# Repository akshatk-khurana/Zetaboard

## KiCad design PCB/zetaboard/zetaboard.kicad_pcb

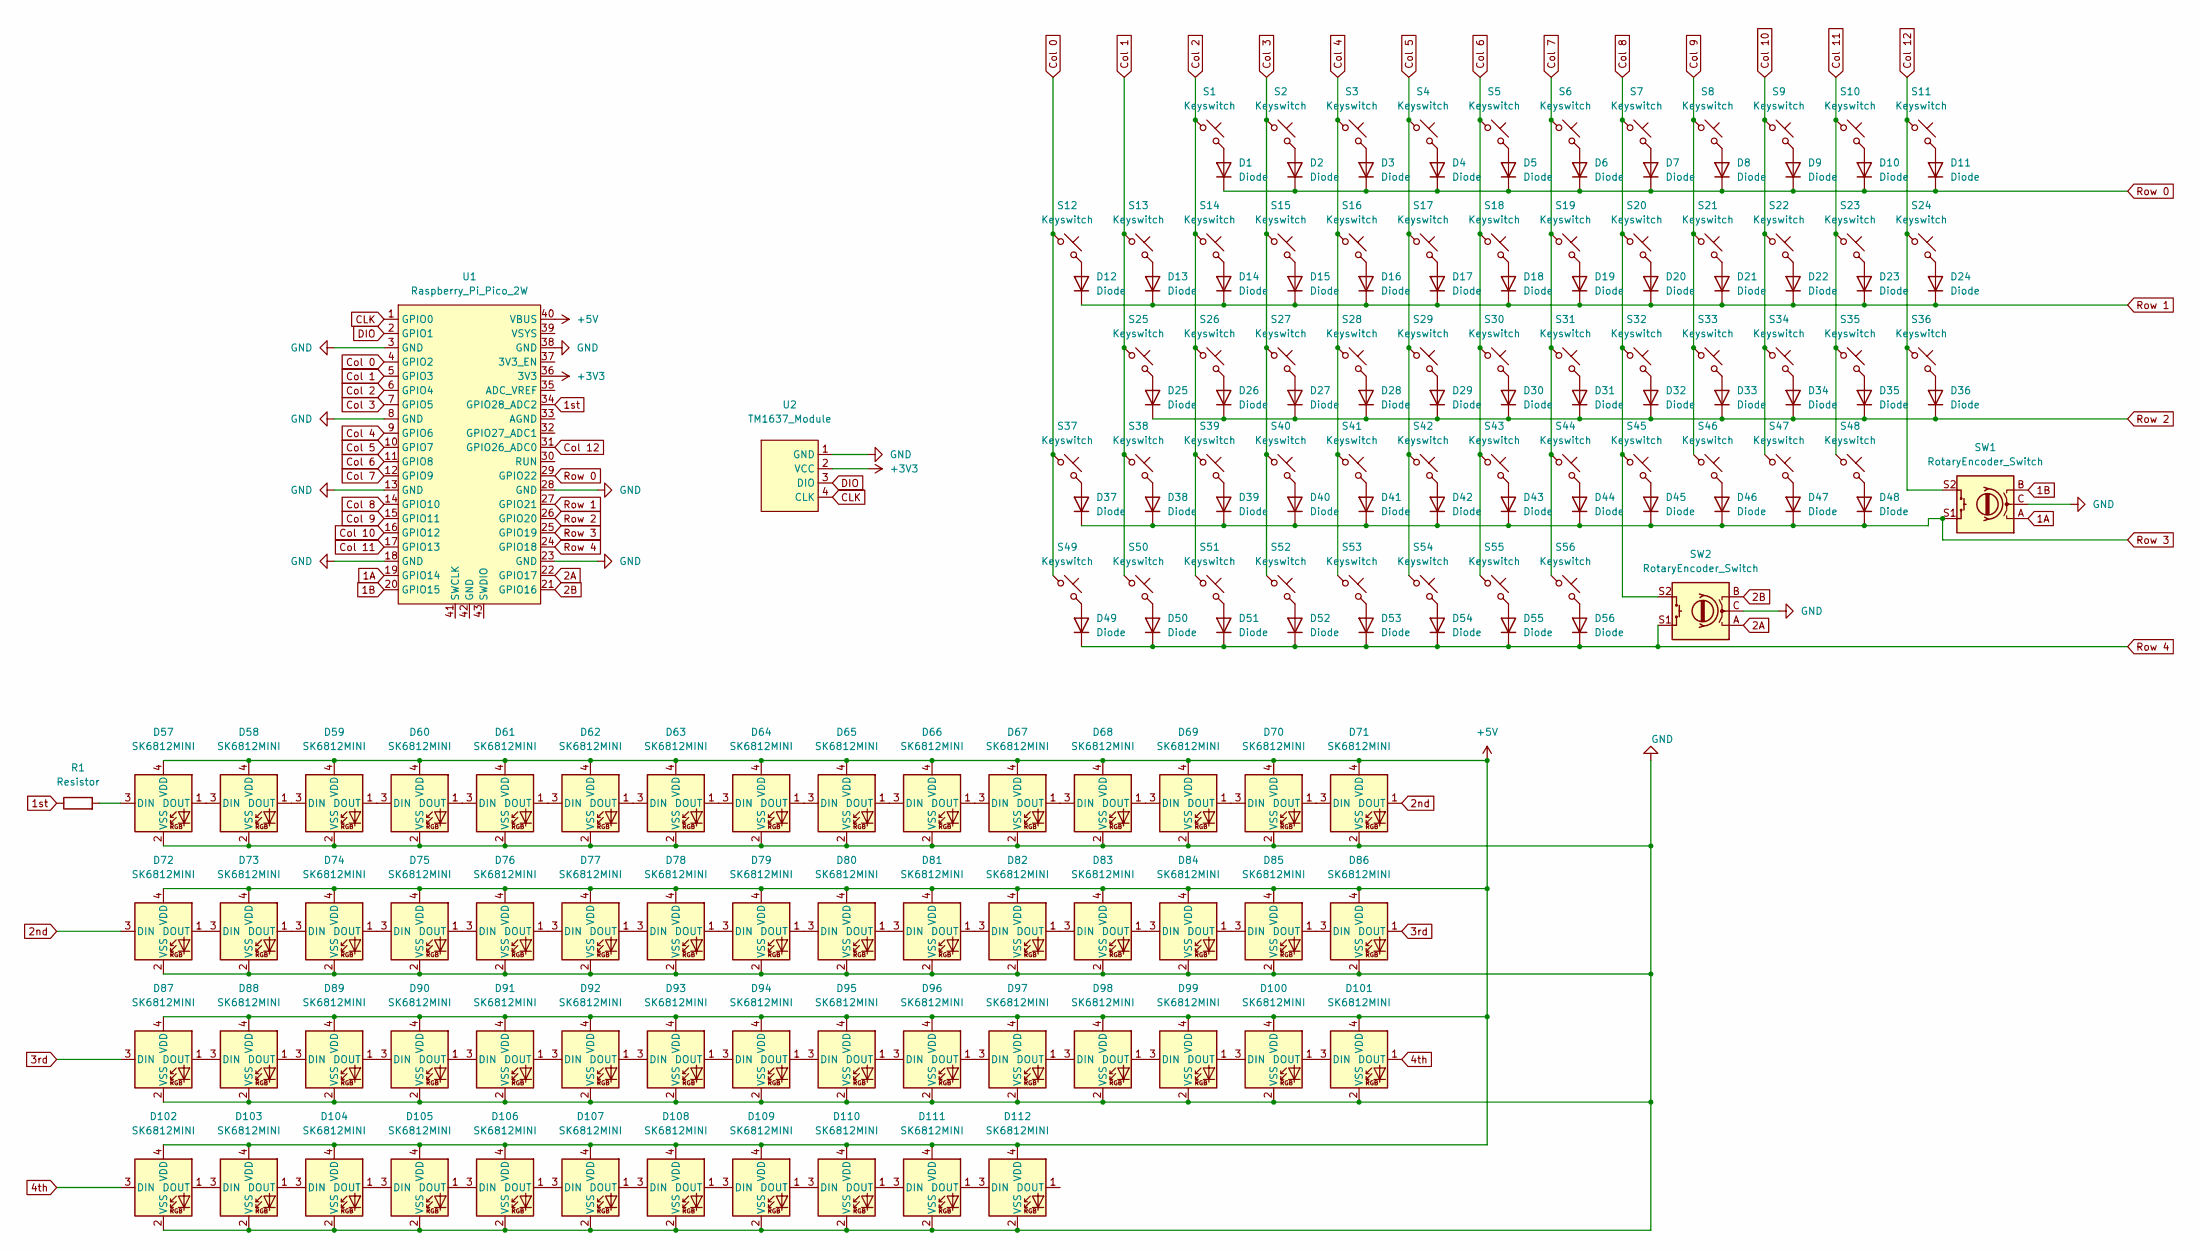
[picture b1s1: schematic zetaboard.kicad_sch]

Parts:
D1, D2, D3, D4, D5, D6, D7, D8, D9, D10, D11, D12, D13, D14, D15, D16, D17, D18, D19, D20, D21, D22, D23, D24, D25, D26, D27, D28, D29, D30, D31, D32, D33, D34, D35, D36, D37, D38, D39, D40, D41, D42, D43, D44, D45, D46, D47, D48, D49, D50, D51, D52, D53, D54, D55, D56: Diode; Diode_DO-35
D57, D58, D59, D60, D61, D62, D63, D64, D65, D66, D67, D68, D69, D70, D71, D72, D73, D74, D75, D76, D77, D78, D79, D80, D81, D82, D83, D84, D85, D86, D87, D88, D89, D90, D91, D92, D93, D94, D95, D96, D97, D98, D99, D100, D101, D102, D103, D104, D105, D106, D107, D108, D109, D110, D111, D112: SK6812MINI; LED_SK6812MINI_PLCC4_3.5x3.5mm_P1.75mm
R1: Resistor; R_0805_2012Metric
S1, S2, S3, S4, S5, S6, S7, S8, S9, S10, S13, S14, S15, S16, S17, S18, S19, S20, S21, S22, S26, S27, S28, S29, S30, S31, S32, S33, S34, S35, S38, S39, S40, S41, S42, S43, S44, S45, S46, S47, S48, S49, S50, S51, S52, S54, S55, S56: Keyswitch; Hotswap_MX_1.00u
S11: Keyswitch; Hotswap_MX_2.00u
S12: Keyswitch; Hotswap_MX_1.50u
S23, S24: Keyswitch; Hotswap_MX_1.25u
S25: Keyswitch; Hotswap_MX_1.75u
S36, S37: Keyswitch; Hotswap_MX_2.25u
S53: Keyswitch; Hotswap_MX_6.25u
SW1, SW2: RotaryEncoder_Switch; RotaryEncoder_Alps_EC11E-Switch_Vertical_H20mm
U1: Raspberry_Pi_Pico_2W; Raspberry_Pi_Pico
U2: TM1637_Module; TM1637 Display Module

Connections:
1A: SW1.A, U1.19 (GPIO14)
1B: SW1.B, U1.20 (GPIO15)
1st: R1.1, U1.34 (GPIO28_ADC2)
2A: SW2.A, U1.22 (GPIO17)
2B: SW2.B, U1.21 (GPIO16)
2nd: D71.1 (DOUT), D72.3 (DIN)
3rd: D86.1 (DOUT), D87.3 (DIN)
4th: D101.1 (DOUT), D102.3 (DIN)
+3V3: U1.36 (3V3), U2.2 (VCC)
+5V: D57.4 (VDD), D58.4 (VDD), D59.4 (VDD), D60.4 (VDD), D61.4 (VDD), D62.4 (VDD), D63.4 (VDD), D64.4 (VDD), D65.4 (VDD), D66.4 (VDD), D67.4 (VDD), D68.4 (VDD), D69.4 (VDD), D70.4 (VDD), D71.4 (VDD), D72.4 (VDD), D73.4 (VDD), D74.4 (VDD), D75.4 (VDD), D76.4 (VDD), D77.4 (VDD), D78.4 (VDD), D79.4 (VDD), D80.4 (VDD), D81.4 (VDD), D82.4 (VDD), D83.4 (VDD), D84.4 (VDD), D85.4 (VDD), D86.4 (VDD), D87.4 (VDD), D88.4 (VDD), D89.4 (VDD), D90.4 (VDD), D91.4 (VDD), D92.4 (VDD), D93.4 (VDD), D94.4 (VDD), D95.4 (VDD), D96.4 (VDD), D97.4 (VDD), D98.4 (VDD), D99.4 (VDD), D100.4 (VDD), D101.4 (VDD), D102.4 (VDD), D103.4 (VDD), D104.4 (VDD), D105.4 (VDD), D106.4 (VDD), D107.4 (VDD), D108.4 (VDD), D109.4 (VDD), D110.4 (VDD), D111.4 (VDD), D112.4 (VDD), U1.40 (VBUS)
CLK: U1.1 (GPIO0), U2.4 (CLK)
Col 0: S12.1, S37.1, S49.1, U1.4 (GPIO2)
Col 1: S13.1, S25.1, S38.1, S50.1, U1.5 (GPIO3)
Col 2: S1.1, S14.1, S26.1, S39.1, S51.1, U1.6 (GPIO4)
Col 3: S2.1, S15.1, S27.1, S40.1, S52.1, U1.7 (GPIO5)
Col 4: S3.1, S16.1, S28.1, S41.1, S53.1, U1.9 (GPIO6)
Col 5: S4.1, S17.1, S29.1, S42.1, S54.1, U1.10 (GPIO7)
Col 6: S5.1, S18.1, S30.1, S43.1, S55.1, U1.11 (GPIO8)
Col 7: S6.1, S19.1, S31.1, S44.1, S56.1, U1.12 (GPIO9)
Col 8: S7.1, S20.1, S32.1, S45.1, SW2.S2, U1.14 (GPIO10)
Col 9: S8.1, S21.1, S33.1, S46.1, U1.15 (GPIO11)
Col 10: S9.1, S22.1, S34.1, S47.1, U1.16 (GPIO12)
Col 11: S10.1, S23.1, S35.1, S48.1, U1.17 (GPIO13)
Col 12: S11.1, S24.1, S36.1, SW1.S2, U1.31 (GPIO26_ADC0)
DIO: U1.2 (GPIO1), U2.3 (DIO)
GND: D57.2 (VSS), D58.2 (VSS), D59.2 (VSS), D60.2 (VSS), D61.2 (VSS), D62.2 (VSS), D63.2 (VSS), D64.2 (VSS), D65.2 (VSS), D66.2 (VSS), D67.2 (VSS), D68.2 (VSS), D69.2 (VSS), D70.2 (VSS), D71.2 (VSS), D72.2 (VSS), D73.2 (VSS), D74.2 (VSS), D75.2 (VSS), D76.2 (VSS), D77.2 (VSS), D78.2 (VSS), D79.2 (VSS), D80.2 (VSS), D81.2 (VSS), D82.2 (VSS), D83.2 (VSS), D84.2 (VSS), D85.2 (VSS), D86.2 (VSS), D87.2 (VSS), D88.2 (VSS), D89.2 (VSS), D90.2 (VSS), D91.2 (VSS), D92.2 (VSS), D93.2 (VSS), D94.2 (VSS), D95.2 (VSS), D96.2 (VSS), D97.2 (VSS), D98.2 (VSS), D99.2 (VSS), D100.2 (VSS), D101.2 (VSS), D102.2 (VSS), D103.2 (VSS), D104.2 (VSS), D105.2 (VSS), D106.2 (VSS), D107.2 (VSS), D108.2 (VSS), D109.2 (VSS), D110.2 (VSS), D111.2 (VSS), D112.2 (VSS), SW1.C, SW2.C, U1.3 (GND), U1.8 (GND), U1.13 (GND), U1.18 (GND), U1.23 (GND), U1.28 (GND), U1.38 (GND), U2.1 (GND)
unnamed: D1.2 (A), S1.2
unnamed: D2.2 (A), S2.2
unnamed: D3.2 (A), S3.2
unnamed: D4.2 (A), S4.2
unnamed: D5.2 (A), S5.2
unnamed: D6.2 (A), S6.2
unnamed: D7.2 (A), S7.2
unnamed: D8.2 (A), S8.2
unnamed: D9.2 (A), S9.2
unnamed: D10.2 (A), S10.2
unnamed: D11.2 (A), S11.2
unnamed: D12.2 (A), S12.2
unnamed: D13.2 (A), S13.2
unnamed: D14.2 (A), S14.2
unnamed: D15.2 (A), S15.2
unnamed: D16.2 (A), S16.2
unnamed: D17.2 (A), S17.2
unnamed: D18.2 (A), S18.2
unnamed: D19.2 (A), S19.2
unnamed: D20.2 (A), S20.2
unnamed: D21.2 (A), S21.2
unnamed: D22.2 (A), S22.2
unnamed: D23.2 (A), S23.2
unnamed: D24.2 (A), S24.2
unnamed: D25.2 (A), S25.2
unnamed: D26.2 (A), S26.2
unnamed: D27.2 (A), S27.2
unnamed: D28.2 (A), S28.2
unnamed: D29.2 (A), S29.2
unnamed: D30.2 (A), S30.2
unnamed: D31.2 (A), S31.2
unnamed: D32.2 (A), S32.2
unnamed: D33.2 (A), S33.2
unnamed: D34.2 (A), S34.2
unnamed: D35.2 (A), S35.2
unnamed: D36.2 (A), S36.2
unnamed: D37.2 (A), S37.2
unnamed: D38.2 (A), S38.2
unnamed: D39.2 (A), S39.2
unnamed: D40.2 (A), S40.2
unnamed: D41.2 (A), S41.2
unnamed: D42.2 (A), S42.2
unnamed: D43.2 (A), S43.2
unnamed: D44.2 (A), S44.2
unnamed: D45.2 (A), S45.2
unnamed: D46.2 (A), S46.2
unnamed: D47.2 (A), S47.2
unnamed: D48.2 (A), S48.2
unnamed: D49.2 (A), S49.2
unnamed: D50.2 (A), S50.2
unnamed: D51.2 (A), S51.2
unnamed: D52.2 (A), S52.2
unnamed: D53.2 (A), S53.2
unnamed: D54.2 (A), S54.2
unnamed: D55.2 (A), S55.2
unnamed: D56.2 (A), S56.2
unnamed: D57.3 (DIN), R1.2
unnamed: D57.1 (DOUT), D58.3 (DIN)
unnamed: D58.1 (DOUT), D59.3 (DIN)
unnamed: D59.1 (DOUT), D60.3 (DIN)
unnamed: D60.1 (DOUT), D61.3 (DIN)
unnamed: D61.1 (DOUT), D62.3 (DIN)
unnamed: D62.1 (DOUT), D63.3 (DIN)
unnamed: D63.1 (DOUT), D64.3 (DIN)
unnamed: D64.1 (DOUT), D65.3 (DIN)
unnamed: D65.1 (DOUT), D66.3 (DIN)
unnamed: D66.1 (DOUT), D67.3 (DIN)
unnamed: D67.1 (DOUT), D68.3 (DIN)
unnamed: D68.1 (DOUT), D69.3 (DIN)
unnamed: D69.1 (DOUT), D70.3 (DIN)
unnamed: D70.1 (DOUT), D71.3 (DIN)
unnamed: D72.1 (DOUT), D73.3 (DIN)
unnamed: D73.1 (DOUT), D74.3 (DIN)
unnamed: D74.1 (DOUT), D75.3 (DIN)
unnamed: D75.1 (DOUT), D76.3 (DIN)
unnamed: D76.1 (DOUT), D77.3 (DIN)
unnamed: D77.1 (DOUT), D78.3 (DIN)
unnamed: D78.1 (DOUT), D79.3 (DIN)
unnamed: D79.1 (DOUT), D80.3 (DIN)
unnamed: D80.1 (DOUT), D81.3 (DIN)
unnamed: D81.1 (DOUT), D82.3 (DIN)
unnamed: D82.1 (DOUT), D83.3 (DIN)
unnamed: D83.1 (DOUT), D84.3 (DIN)
unnamed: D84.1 (DOUT), D85.3 (DIN)
unnamed: D85.1 (DOUT), D86.3 (DIN)
unnamed: D87.1 (DOUT), D88.3 (DIN)
unnamed: D88.1 (DOUT), D89.3 (DIN)
unnamed: D89.1 (DOUT), D90.3 (DIN)
unnamed: D90.1 (DOUT), D91.3 (DIN)
unnamed: D91.1 (DOUT), D92.3 (DIN)
unnamed: D92.1 (DOUT), D93.3 (DIN)
unnamed: D93.1 (DOUT), D94.3 (DIN)
unnamed: D94.1 (DOUT), D95.3 (DIN)
unnamed: D95.1 (DOUT), D96.3 (DIN)
unnamed: D96.1 (DOUT), D97.3 (DIN)
unnamed: D97.1 (DOUT), D98.3 (DIN)
unnamed: D98.1 (DOUT), D99.3 (DIN)
unnamed: D99.1 (DOUT), D100.3 (DIN)
unnamed: D100.1 (DOUT), D101.3 (DIN)
unnamed: D102.1 (DOUT), D103.3 (DIN)
unnamed: D103.1 (DOUT), D104.3 (DIN)
unnamed: D104.1 (DOUT), D105.3 (DIN)
unnamed: D105.1 (DOUT), D106.3 (DIN)
unnamed: D106.1 (DOUT), D107.3 (DIN)
unnamed: D107.1 (DOUT), D108.3 (DIN)
unnamed: D108.1 (DOUT), D109.3 (DIN)
unnamed: D109.1 (DOUT), D110.3 (DIN)
unnamed: D110.1 (DOUT), D111.3 (DIN)
unnamed: D111.1 (DOUT), D112.3 (DIN)
Row 0: D1.1 (K), D2.1 (K), D3.1 (K), D4.1 (K), D5.1 (K), D6.1 (K), D7.1 (K), D8.1 (K), D9.1 (K), D10.1 (K), D11.1 (K), U1.29 (GPIO22)
Row 1: D12.1 (K), D13.1 (K), D14.1 (K), D15.1 (K), D16.1 (K), D17.1 (K), D18.1 (K), D19.1 (K), D20.1 (K), D21.1 (K), D22.1 (K), D23.1 (K), D24.1 (K), U1.27 (GPIO21)
Row 2: D25.1 (K), D26.1 (K), D27.1 (K), D28.1 (K), D29.1 (K), D30.1 (K), D31.1 (K), D32.1 (K), D33.1 (K), D34.1 (K), D35.1 (K), D36.1 (K), U1.26 (GPIO20)
Row 3: D37.1 (K), D38.1 (K), D39.1 (K), D40.1 (K), D41.1 (K), D42.1 (K), D43.1 (K), D44.1 (K), D45.1 (K), D46.1 (K), D47.1 (K), D48.1 (K), SW1.S1, U1.25 (GPIO19)
Row 4: D49.1 (K), D50.1 (K), D51.1 (K), D52.1 (K), D53.1 (K), D54.1 (K), D55.1 (K), D56.1 (K), SW2.S1, U1.24 (GPIO18)

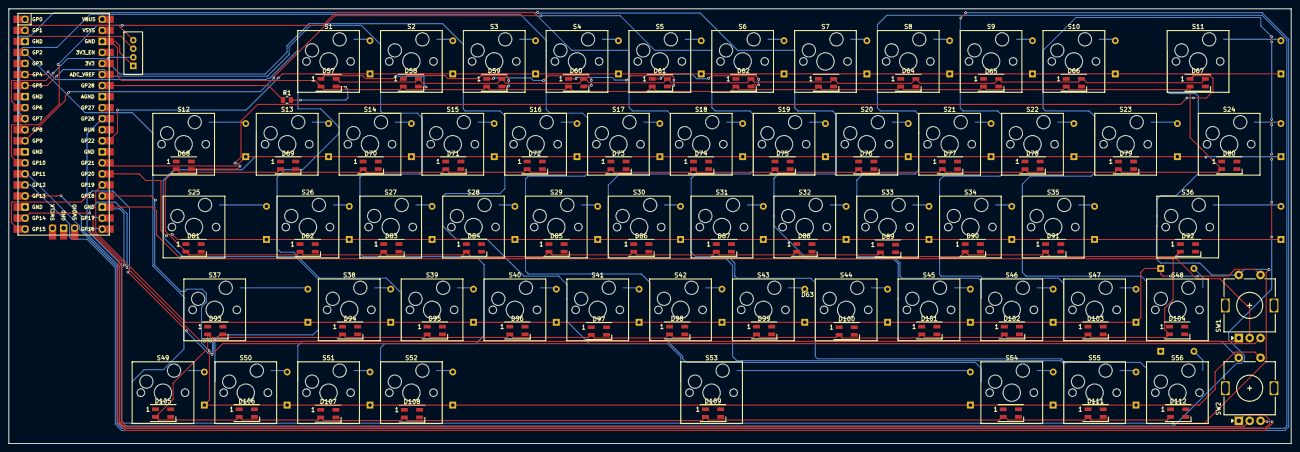
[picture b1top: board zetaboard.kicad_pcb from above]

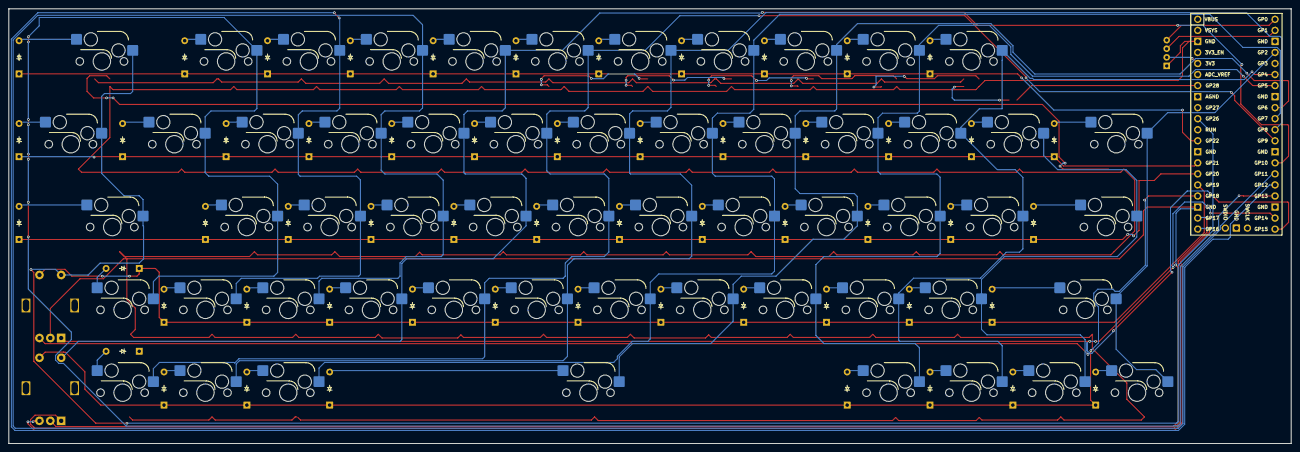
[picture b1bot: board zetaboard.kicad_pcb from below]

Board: 2 copper layers, 295.0 x 100.0 mm, 173 parts (56 on the bottom side), 140 nets.

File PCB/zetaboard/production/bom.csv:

Designator,Footprint,Quantity,Value,LCSC Part #
"D1, D10, D11, D12, D13, D14, D15, D16, D17, D18, D19, D2, D20, D21, D22, D23, D24, D25, D26, D27, D28, D29, D3, D30, D31, D32, D33, D34, D35, D36, D37, D38, D39, D4, D40, D41, D42, D43, D44, D45, D46, D47, D48, D49, D5, D50, D51, D52, D53, D54, D55, D56, D6, D7, D8, D9",Diode_DO-35,56,Diode,
"D100, D101, D102, D103, D104, D105, D106, D107, D108, D109, D110, D111, D112, D57, D58, D59, D60, D61, D62, D63, D64, D65, D66, D67, D68, D69, D70, D71, D72, D73, D74, D75, D76, D77, D78, D79, D80, D81, D82, D83, D84, D85, D86, D87, D88, D89, D90, D91, D92, D93, D94, D95, D96, D97, D98, D99",LED_SK6812MINI_PLCC4_3.5x3.5mm_P1.75mm,56,SK6812MINI,
R1,0805,1,Resistor,
"S1, S10, S13, S14, S15, S16, S17, S18, S19, S2, S20, S21, S22, S26, S27, S28, S29, S3, S30, S31, S32, S33, S34, S35, S38, S39, S4, S40, S41, S42, S43, S44, S45, S46, S47, S48, S49, S5, S50, S51, S52, S54, S55, S56, S6, S7, S8, S9",Hotswap_MX_1.00u,48,Keyswitch,
S11,Hotswap_MX_2.00u,1,Keyswitch,
S12,Hotswap_MX_1.50u,1,Keyswitch,
"S23, S24",Hotswap_MX_1.25u,2,Keyswitch,
S25,Hotswap_MX_1.75u,1,Keyswitch,
"S36, S37",Hotswap_MX_2.25u,2,Keyswitch,
S53,Hotswap_MX_6.25u,1,Keyswitch,
"SW1, SW2",RotaryEncoder_Alps_EC11E-Switch_Vertical_H20mm,2,RotaryEncoder_Switch,
U1,Raspberry_Pi_Pico,1,Raspberry_Pi_Pico_2W,
U2,TM1637 Display Module,1,TM1637_Module,

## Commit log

2025-06-04 Setup
2025-06-04 Ideation
2025-06-05 More ideation and thinking about parts
2025-06-07 Almost finished BOM
2025-06-07 Changed .gitignore
2025-06-09 Starting the schematic
2025-06-10 Schematic finished and PCB started.
2025-06-11 Save commit just in case I mess something up with removing the capacitors
2025-06-11 Still on the PCB
2025-06-15 (Basically) finished PCB and started work on plate
2025-06-18 Finally finished the case! Onto firmware now...
